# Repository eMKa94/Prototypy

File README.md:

# Prototypy

This repository contains projects modules ( schematics with PCB's layouts ).
The idea is to simply use this schematics as a hierarchical schematics in kicad projects and PCB layouts as reference.

example:

"3V_4I_ac_afe" consist of submodules "ac_i_afe" & "ac_v_afe" ( schematics ). PCB design in kicad cannot be modular so the PCB have to be designed individualy for each design.

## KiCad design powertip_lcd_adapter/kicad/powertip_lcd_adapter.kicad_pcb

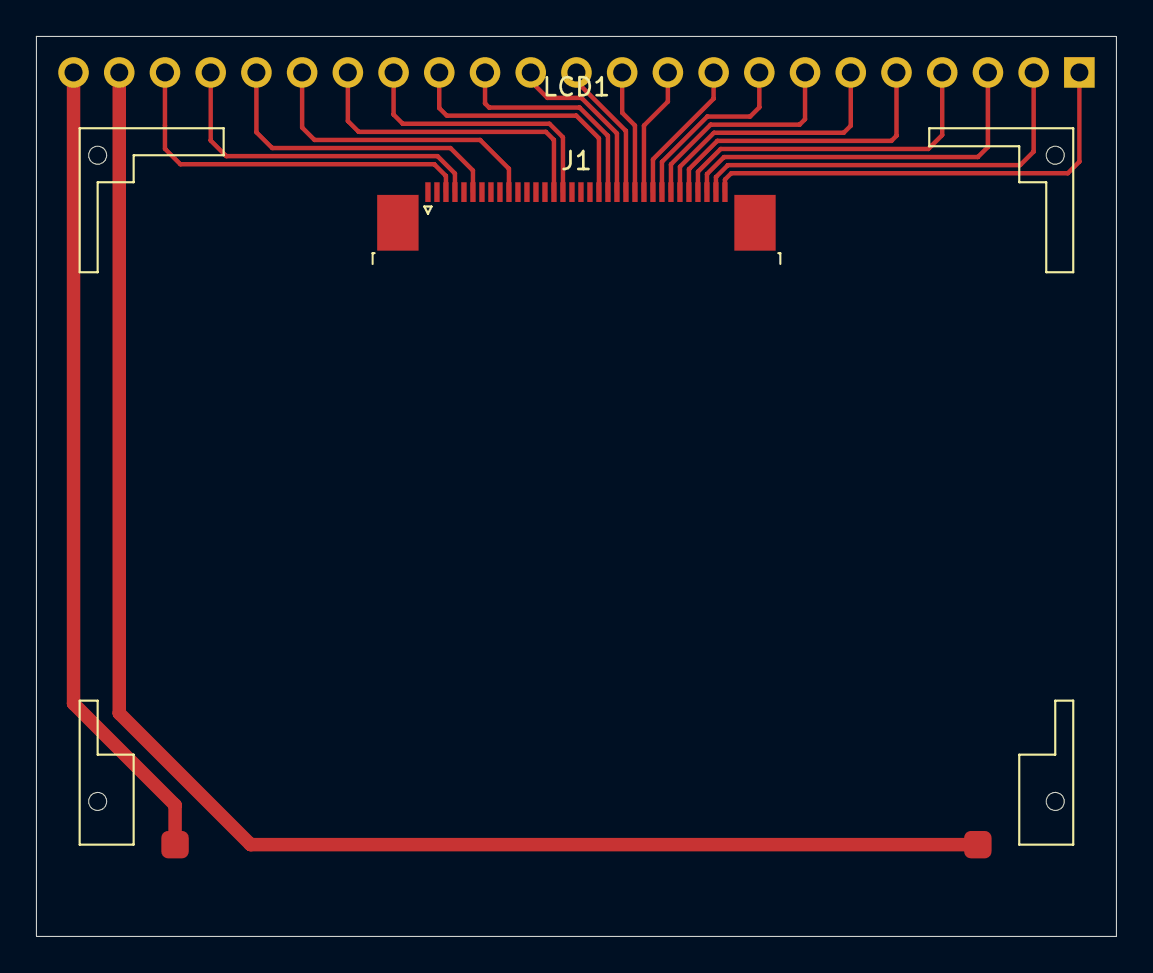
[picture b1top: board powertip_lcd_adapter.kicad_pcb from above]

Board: 2 copper layers, 60.0 x 50.0 mm, 3 parts (1 on the bottom side), 23 nets.

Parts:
J1: Conn_01x34; TE_3-1734839-4_1x34-1MP_P0.5mm_Horizontal
J2: Conn_01x23; PinHeader_1x23_P2.54mm_Vertical
LCD1: lcd_module; LCD_PE12864WRF-055-H-Q

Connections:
/A: J2.22, LCD1.2
/A_0: J1.32, J2.3
/C86: J1.4, J2.20
/CS_1: J1.34, J2.1
/D_0: J1.29, J2.6
/D_1: J1.28, J2.7
/D_2: J1.27, J2.8
/D_3: J1.26, J2.9
/D_4: J1.25, J2.10
/D_5: J1.24, J2.11
/D_6: J1.23, J2.12
/D_7: J1.22, J2.13
/K: J2.23, LCD1.1
/P_S: J1.3, J2.21
/RD: J1.30, J2.5
/RST: J1.33, J2.2
/VDD: J1.21, J2.14
/VG: J1.6, J2.19
/VM: J1.10, J2.18
/VSS: J1.20, J2.15
/V_0: J1.16, J2.16
/WR: J1.31, J2.4
/XV_0: J1.15, J2.17

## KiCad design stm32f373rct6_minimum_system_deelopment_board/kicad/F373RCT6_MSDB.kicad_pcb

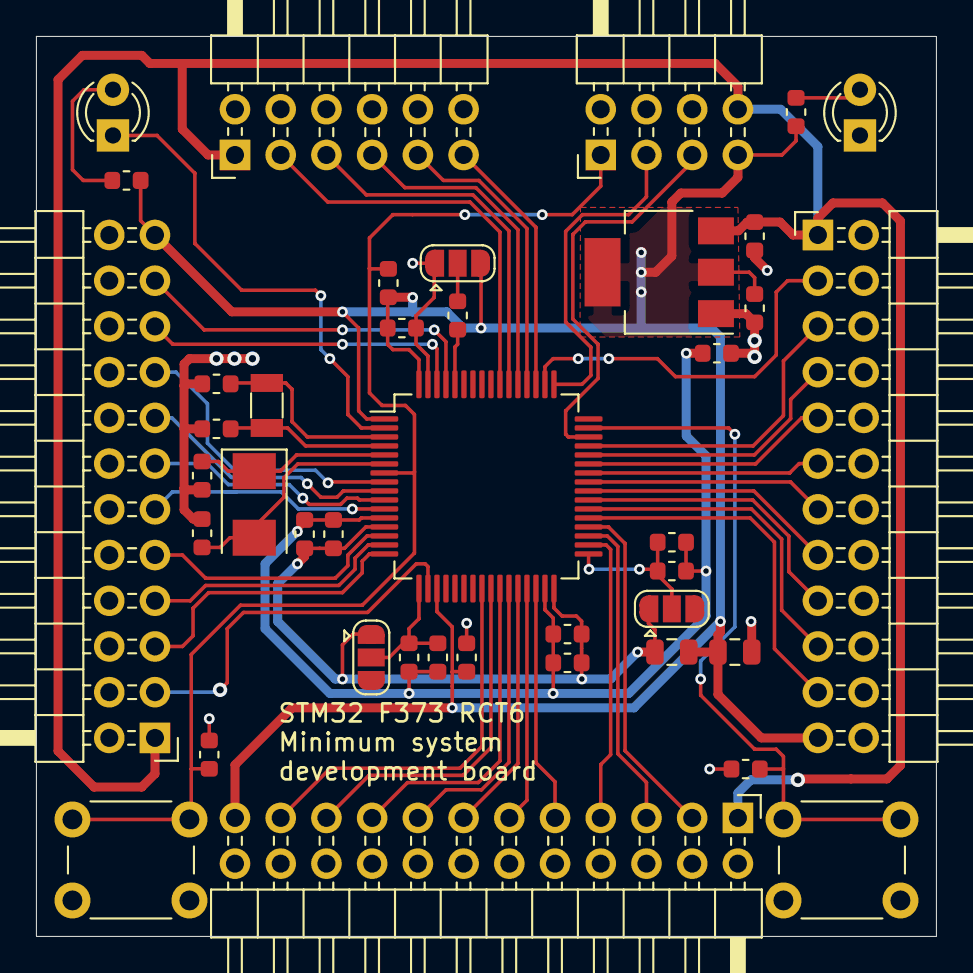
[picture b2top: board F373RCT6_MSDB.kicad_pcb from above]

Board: 2 copper layers, 50.0 x 50.0 mm, 41 parts (0 on the bottom side), 55 nets.

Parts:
C1, C8, C10, C12, C17: 10n; C_0603_1608Metric
C2, C3: 22p; C_0603_1608Metric
C4, C5: 12p; C_0603_1608Metric
C6, C9, C11, C13, C18: 1u; C_0603_1608Metric
C7, C14, C15, C19: 100n; C_0603_1608Metric
C16: 4,7u; C_0805_2012Metric
D1, D2: LED; LED_D3.0mm
J1: Conn_02x04_Odd_Even; PinHeader_2x04_P2.54mm_Horizontal
J2: Conn_02x06_Odd_Even; PinHeader_2x06_P2.54mm_Horizontal
J3, J4, J5: Conn_02x12_Odd_Even; PinHeader_2x12_P2.54mm_Horizontal
JP1: Jumper_VREFSD; SolderJumper-3_P1.3mm_Open_RoundedPad1.0x1.5mm
JP2: Jumper_VREF; SolderJumper-3_P1.3mm_Open_RoundedPad1.0x1.5mm
JP3: Jumper_BOOT0; SolderJumper-3_P1.3mm_Open_RoundedPad1.0x1.5mm
L1: 10u; L_0805_2012Metric
R1, R2: 10K; R_0603_1608Metric
R3: 0; R_0603_1608Metric
R4, R5: 510; R_0603_1608Metric
SW1: SW_RESET; SW_PUSH_6mm_H7.3mm
SW2: SW_F6; SW_PUSH_6mm_H7.3mm
U1: STM32F373RCTx; LQFP-64_10x10mm_P0.5mm
U2: LM1117-3.3; SOT-223-3_TabPin2
Y1: 8M; Crystal_SMD_5032-2Pin_5.0x3.2mm
Y2: 32768; Crystal_SMD_3215-2Pin_3.2x1.5mm

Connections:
+5V: C17.1, J1.8, J2.1, J3.1, J4.1, J5.1, U2.3
/A_0: J3.9, U1.14
/A_1: J3.7, U1.15
/A_2: J3.5, U1.16
/A_3: J3.3, U1.18
/A_8: J5.13, U1.41
/A_9: J5.11, U1.42
/A_10: J5.9, U1.43
/A_11: J5.7, U1.44
/A_12: J5.5, U1.45
/A_15: J5.3, U1.50
/B_0: J4.17, U1.26
/B_1: J4.15, U1.27
/B_2: J4.13, U1.28
/B_3: J2.3, U1.55
/B_8: J3.21, U1.61
/B_9: J3.19, U1.62
/B_14: J4.7, U1.34
/B_15: J4.5, U1.35
/C_0: J3.17, U1.8
/C_1: J3.15, U1.9
/C_2: J3.13, U1.10
/C_3: J3.11, U1.11
/C_4: J4.21, U1.24
/C_5: J4.19, U1.25
/C_6: J5.21, U1.37
/C_7: J5.19, U1.38
/C_8: J5.17, U1.39
/C_9: J5.15, U1.40
/C_10: J2.11, U1.51
/C_11: J2.9, U1.52
/C_12: J2.7, U1.53
/C_13: D1.1, U1.2
/D_2: J2.5, U1.54
/D_8: J4.3, U1.36
/E_8: J4.11, U1.29
/E_9: J4.9, U1.30
/F_6: C19.2, SW2.1, U1.47
/STM32F373RCT6/BOOT0: JP3.2, R1.1
/STM32F373RCT6/GNDA: C1.2, C6.2, C8.2, C9.2, C10.2, C11.2, C12.2, C13.2, R3.2, U1.12, U1.31
/STM32F373RCT6/VDDA: C1.1, C6.1, C8.1, C9.1, JP1.1, JP2.1, L1.1, U1.13, U1.32
/STM32F373RCT6/VREF+: C12.1, C13.1, JP2.2, U1.17
/STM32F373RCT6/VREFSD+: C10.1, C11.1, JP1.2, U1.33
/SWD_CLK: J1.3, U1.49
/SWD_DIO: J1.5, U1.46
/~uC_RESET: C7.2, J1.1, R2.1, SW1.1, U1.7
GND: C2.2, C3.2, C4.2, C5.2, C7.1, C14.2, C15.2, C16.2, C17.2, C18.2, C19.1, D2.1, J1.2, J1.4, J1.6, J2.2, J2.4, J2.6, J2.8, J2.10, J2.12, J3.2, J3.4, J3.6, J3.8, J3.10, J3.12, J3.14, J3.16, J3.18, J3.20, J3.22, J3.24, J4.2, J4.4, J4.6, J4.8, J4.10, J4.12, J4.14, J4.16, J4.18, J4.20, J4.22, J4.24, J5.2, J5.4, J5.6, J5.8, J5.10, J5.12, J5.14, J5.16, J5.18, J5.20, J5.22, J5.24, JP3.1, R3.1, SW1.2, SW2.2, U1.63, U2.1
unnamed: C2.1, U1.5, Y1.1
unnamed: C3.1, U1.6, Y1.2
unnamed: C4.1, U1.3, Y2.1
unnamed: C5.1, U1.4, Y2.2
unnamed: D1.2, R4.2
unnamed: D2.2, R5.2
unnamed: R1.2, U1.60
VDD: C14.1, C15.1, C16.1, C18.1, J1.7, J3.23, J4.23, J5.23, JP3.3, L1.2, R2.2, R4.1, R5.1, U1.1, U1.19, U1.64, U2.2

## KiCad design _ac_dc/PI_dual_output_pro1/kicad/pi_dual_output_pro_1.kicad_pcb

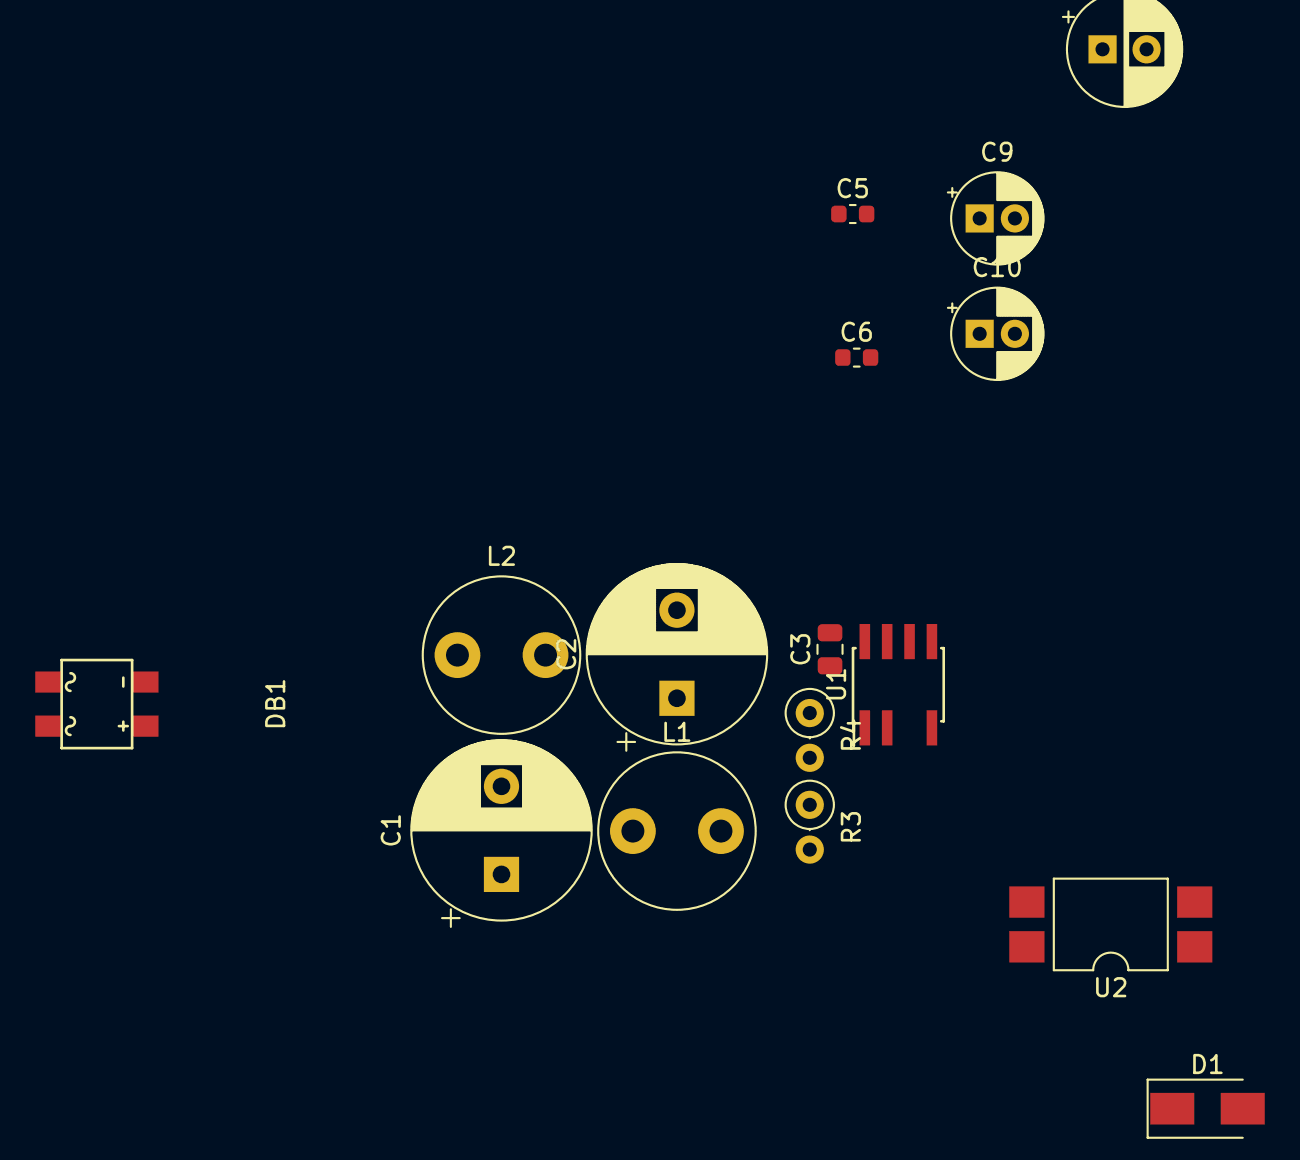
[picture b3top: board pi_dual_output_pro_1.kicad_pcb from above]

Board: 2 copper layers, 16 parts (0 on the bottom side), 9 nets, no tracks yet.

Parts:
C1, C2: 6,8u; CP_Radial_D10.0mm_P5.00mm
C3: 10u; C_0805_2012Metric
C5, C6: 560p; C_0603_1608Metric
C7: 220u; CP_Radial_D6.3mm_P2.50mm
C9, C10: 100u; CP_Radial_D5.0mm_P2.00mm
D1: SMB6F100AY; D_SMA
DB1: D_Bridge_AA+-; MiniDIP
L1, L2: 1m; L_Radial_D8.7mm_P5.00mm_Fastron_07HCP
R3, R4: 2M; R_Axial_DIN0207_L6.3mm_D2.5mm_P2.54mm_Vertical
U1: TNY285D; PowerIntegrations_SO-8C
U2: LTV-817S; SMDIP-4_W9.53mm

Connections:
/hv_dc_+: C1.1, DB1.3, L1.1
/hv_dc_-: C1.2, DB1.4, L2.1
unnamed: C2.1, D1.1, L1.2, R3.2
unnamed: C2.2, C3.2, L2.2, U1.5, U1.6, U1.7, U1.8, U2.3
unnamed: C3.1, U1.2
unnamed: C5.1, C7.1
unnamed: C7.2, C9.2
unnamed: R3.1, R4.2
unnamed: R4.1, U1.1, U2.4

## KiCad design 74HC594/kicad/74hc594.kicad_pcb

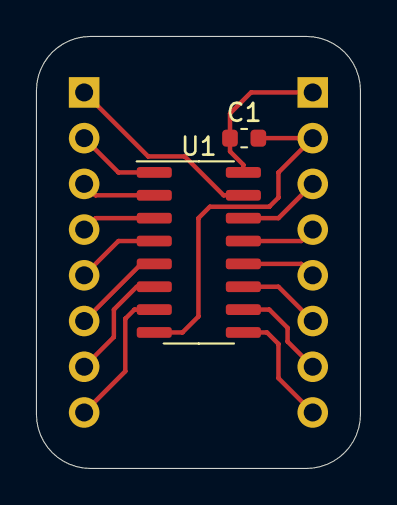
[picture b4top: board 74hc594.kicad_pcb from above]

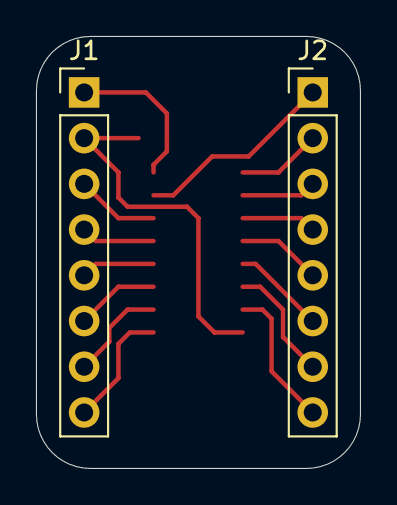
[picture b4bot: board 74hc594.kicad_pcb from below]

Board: 2 copper layers, 18.0 x 24.0 mm, 4 parts (2 on the bottom side), 16 nets.

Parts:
C1: C; C_0603_1608Metric
J1, J2: Conn_01x08; PinHeader_1x08_P2.54mm_Vertical
U1: 74HC595; SOIC-16_3.9x9.9mm_P1.27mm

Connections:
/GND: C1.2, J1.2, U1.8
/Q_A: J2.1, U1.15
/Q_B: J2.2, U1.1
/Q_C: J2.3, U1.2
/Q_D: J2.4, U1.3
/Q_E: J2.5, U1.4
/Q_F: J2.6, U1.5
/Q_G: J2.7, U1.6
/Q_H: J2.8, U1.7
/Q_H': J1.8, U1.9
/RCLK: J1.5, U1.12
/SER: J1.3, U1.14
/SRCLK: J1.6, U1.11
/VCC: C1.1, J1.1, U1.16
/~OE: J1.4, U1.13
/~SRCLR: J1.7, U1.10

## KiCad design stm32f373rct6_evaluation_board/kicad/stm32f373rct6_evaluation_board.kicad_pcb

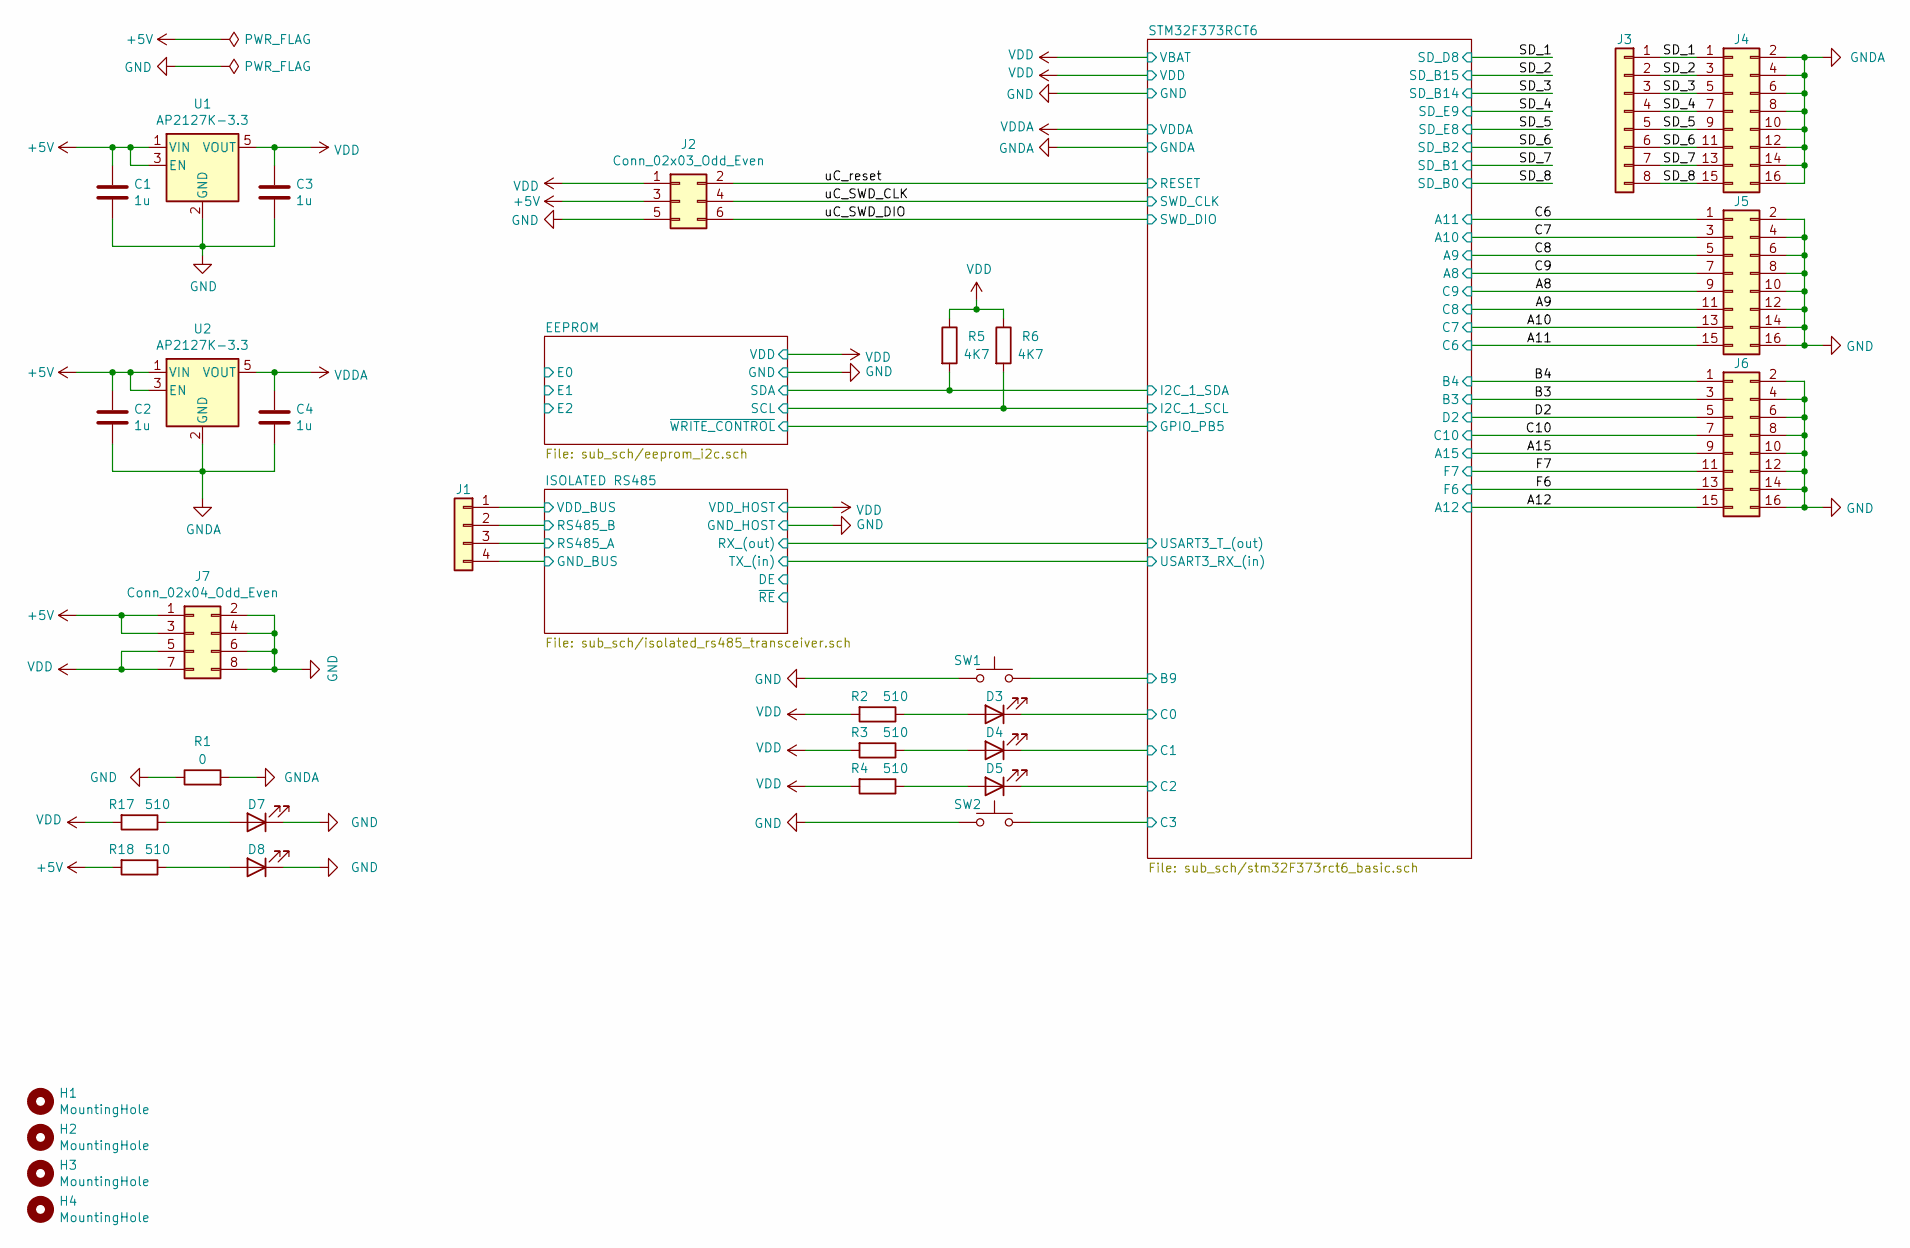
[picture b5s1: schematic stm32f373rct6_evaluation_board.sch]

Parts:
C1, C2, C3, C4: 1u; C_0603_1608Metric
D3, D4, D5, D7, D8: LED; LED_0805_2012Metric
H1, H2, H3, H4: MountingHole; MountingHole_3.2mm_M3
J1: RS485_connector; PinHeader_1x04_P2.54mm_Horizontal
J2: Conn_02x03_Odd_Even; PinHeader_2x03_P2.54mm_Horizontal
J3: Conn_01x08; PinHeader_1x08_P2.54mm_Vertical
J4: Conn_02x08_Odd_Even; PinHeader_2x08_P2.54mm_Horizontal
J5, J6: Conn_02x08_Odd_Even; PinHeader_2x08_P2.54mm_Vertical
J7: Conn_02x04_Odd_Even; PinHeader_2x04_P2.54mm_Vertical
R1: 0; R_0603_1608Metric
R2, R3, R4, R17, R18: 510; R_0402_1005Metric
R5, R6: 4K7; R_0402_1005Metric
SW1, SW2: SW; SW_SPST_B3U-1000P
U1, U2: AP2127K-3.3; SOT-23-5

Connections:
+5V: C1.1, C2.1, J2.3, J7.1, J7.3, R18.2, U1.1 (VIN), U1.3 (EN), U2.1 (VIN), U2.3 (EN)
/A8: J5.9; also elsewhere on the board
/A9: J5.11; also elsewhere on the board
/A10: J5.13; also elsewhere on the board
/A11: J5.15; also elsewhere on the board
/A15: J6.9; also elsewhere on the board
/B3: J6.3; also elsewhere on the board
/B4: J6.1; also elsewhere on the board
/C6: J5.1; also elsewhere on the board
/C7: J5.3; also elsewhere on the board
/C8: J5.5; also elsewhere on the board
/C9: J5.7; also elsewhere on the board
/C10: J6.7; also elsewhere on the board
/D2: J6.5; also elsewhere on the board
/F6: J6.13; also elsewhere on the board
/F7: J6.11; also elsewhere on the board
/ISOLATED RS485/GND_BUS: J1.4; also elsewhere on the board
/ISOLATED RS485/RS485_A: J1.3; also elsewhere on the board
/ISOLATED RS485/RS485_B: J1.2; also elsewhere on the board
/ISOLATED RS485/VDD_BUS: J1.1; also elsewhere on the board
/SD_1: J3.1, J4.1; also elsewhere on the board
/SD_2: J3.2, J4.3; also elsewhere on the board
/SD_3: J3.3, J4.5; also elsewhere on the board
/SD_4: J3.4, J4.7; also elsewhere on the board
/SD_5: J3.5, J4.9; also elsewhere on the board
/SD_6: J3.6, J4.11; also elsewhere on the board
/SD_7: J3.7, J4.13; also elsewhere on the board
/SD_8: J3.8, J4.15; also elsewhere on the board
/STM32F373RCT6/B9: SW1.2; also elsewhere on the board
/STM32F373RCT6/C0: D3.1 (K); also elsewhere on the board
/STM32F373RCT6/C1: D4.1 (K); also elsewhere on the board
/STM32F373RCT6/C2: D5.1 (K); also elsewhere on the board
/STM32F373RCT6/C3: SW2.2; also elsewhere on the board
/STM32F373RCT6/I2C_1_SCL: R6.2; also elsewhere on the board
/STM32F373RCT6/I2C_1_SDA: R5.2; also elsewhere on the board
/uC_SWD_CLK: J2.4; also elsewhere on the board
/uC_SWD_DIO: J2.6; also elsewhere on the board
/uC_reset: J2.2; also elsewhere on the board
GND: C1.2, C3.2, D7.1 (K), D8.1 (K), J2.5, J5.2, J5.4, J5.6, J5.8, J5.10, J5.12, J5.14, J5.16, J6.2, J6.4, J6.6, J6.8, J6.10, J6.12, J6.14, J6.16, J7.2, J7.4, J7.6, J7.8, R1.1, SW1.1, SW2.1, U1.2 (GND); also elsewhere on the board
GNDA: C2.2, C4.2, J4.2, J4.4, J4.6, J4.8, J4.10, J4.12, J4.14, J4.16, R1.2, U2.2 (GND); also elsewhere on the board
GPIO_A12: J6.15; also elsewhere on the board
unnamed: D3.2 (A), R2.1
unnamed: D4.2 (A), R3.1
unnamed: D5.2 (A), R4.1
unnamed: D7.2 (A), R17.1
unnamed: D8.2 (A), R18.1
VDD: C3.1, J2.1, J7.5, J7.7, R2.2, R3.2, R4.2, R5.1, R6.1, R17.2, U1.5 (VOUT); also elsewhere on the board
VDDA: C4.1, U2.5 (VOUT); also elsewhere on the board

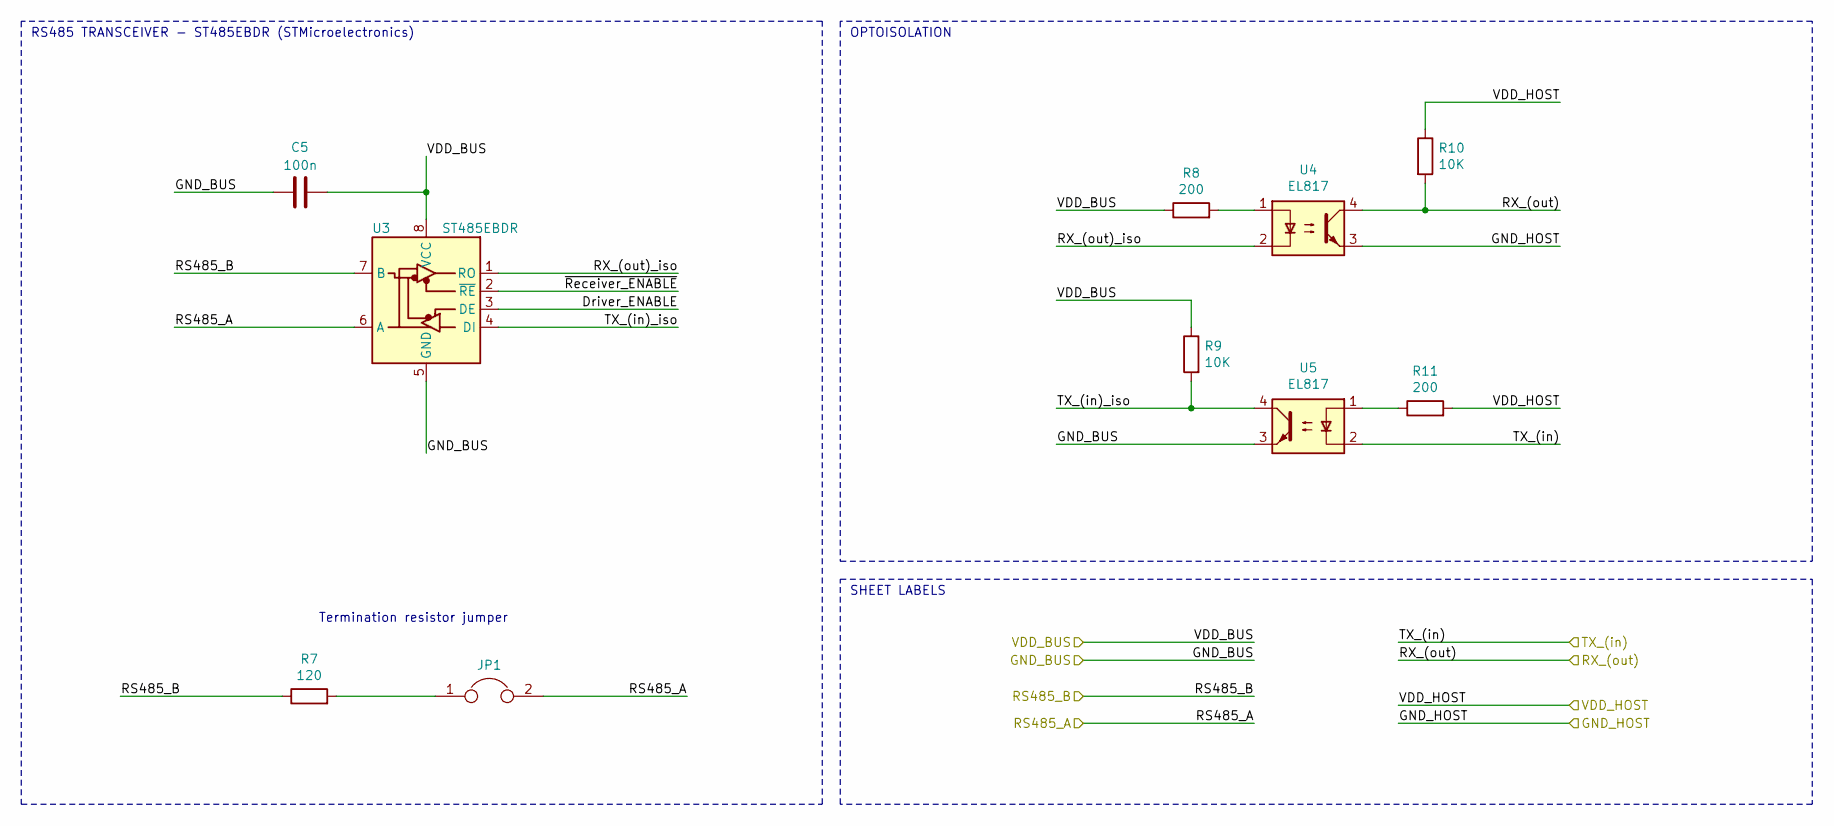
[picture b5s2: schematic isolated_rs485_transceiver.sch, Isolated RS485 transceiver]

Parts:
C5: 100n; C_0603_1608Metric
JP1: Jumper; SolderJumper-2_P1.3mm_Open_RoundedPad1.0x1.5mm
R7: 120; R_0603_1608Metric
R8, R11: 200; R_0603_1608Metric
R9, R10: 10K; R_0603_1608Metric
U3: ST485EBDR; SOIC-8_3.9x4.9mm_P1.27mm
U4, U5: EL817; DIP-4_W7.62mm

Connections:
/ISOLATED RS485/Driver_ENABLE: U3.3 (DE)
/ISOLATED RS485/GND_BUS: C5.1, U3.5 (GND), U5.3; also elsewhere on the board
/ISOLATED RS485/RS485_A: JP1.2, U3.6 (A); also elsewhere on the board
/ISOLATED RS485/RS485_B: R7.1, U3.7 (B); also elsewhere on the board
/ISOLATED RS485/RX_(out): R10.2, U4.4; also elsewhere on the board
/ISOLATED RS485/RX_(out)_iso: U3.1 (RO), U4.2
/ISOLATED RS485/TX_(in): U5.2; also elsewhere on the board
/ISOLATED RS485/TX_(in)_iso: R9.2, U3.4 (DI), U5.4
/ISOLATED RS485/VDD_BUS: C5.2, R8.1, R9.1, U3.8 (VCC); also elsewhere on the board
/ISOLATED RS485/~Receiver_ENABLE: U3.2 (~RE)
GND: U4.3; also elsewhere on the board
unnamed: JP1.1, R7.2
unnamed: R8.2, U4.1
unnamed: R11.1, U5.1
VDD: R10.1, R11.2; also elsewhere on the board

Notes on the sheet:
OPTOISOLATION
RS485 TRANSCEIVER - ST485EBDR (STMicroelectronics)
SHEET LABELS
Termination resistor jumper

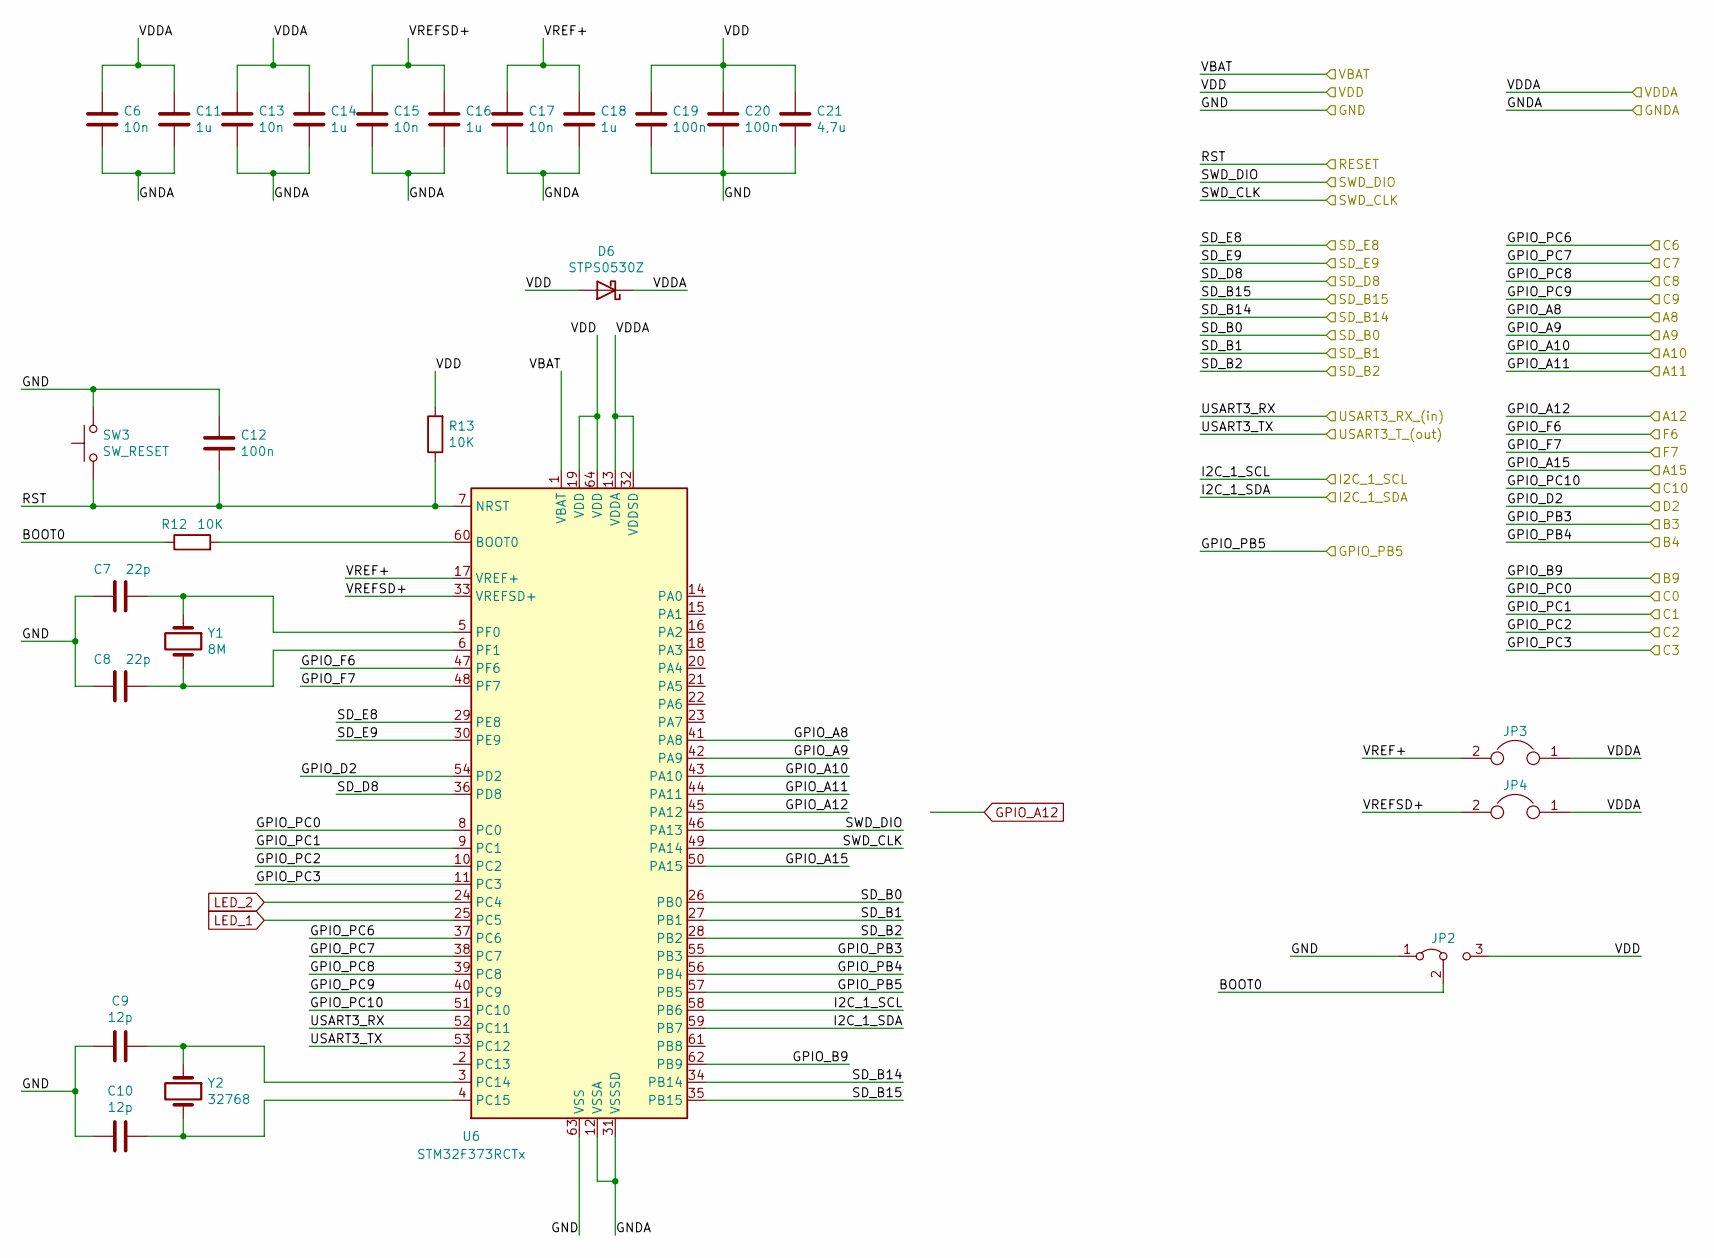
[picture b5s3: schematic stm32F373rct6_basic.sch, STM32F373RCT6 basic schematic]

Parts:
C6, C13, C15, C17: 10n; C_0402_1005Metric
C7, C8: 22p; C_0603_1608Metric
C9, C10: 12p; C_0603_1608Metric
C11, C14, C16, C18: 1u; C_0603_1608Metric
C12: 100n; C_0603_1608Metric
C19, C20: 100n; C_0402_1005Metric
C21: 4,7u; C_0805_2012Metric
D6: STPS0530Z; D_SOD-323
JP2: Jumper_BOOT0; SolderJumper-3_P1.3mm_Open_RoundedPad1.0x1.5mm
JP3, JP4: Jumper; SolderJumper-2_P1.3mm_Open_RoundedPad1.0x1.5mm
R12, R13: 10K; R_0402_1005Metric
SW3: SW_RESET; SW_SPST_B3U-1000P
U6: STM32F373RCTx; LQFP-64_10x10mm_P0.5mm
Y1: 8M; Crystal_SMD_5032-2Pin_5.0x3.2mm; PART_NUMBER LF XTAL003151
Y2: 32768; Crystal_SMD_3215-2Pin_3.2x1.5mm

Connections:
/A8: U6.40 (PC9); also elsewhere on the board
/A9: U6.39 (PC8); also elsewhere on the board
/A10: U6.38 (PC7); also elsewhere on the board
/A11: U6.37 (PC6); also elsewhere on the board
/A15: U6.50 (PA15); also elsewhere on the board
/B3: U6.55 (PB3); also elsewhere on the board
/B4: U6.56 (PB4); also elsewhere on the board
/C6: U6.44 (PA11); also elsewhere on the board
/C7: U6.43 (PA10); also elsewhere on the board
/C8: U6.42 (PA9); also elsewhere on the board
/C9: U6.41 (PA8); also elsewhere on the board
/C10: U6.51 (PC10); also elsewhere on the board
/D2: U6.54 (PD2); also elsewhere on the board
/F6: U6.47 (PF6); also elsewhere on the board
/F7: U6.48 (PF7); also elsewhere on the board
/ISOLATED RS485/RX_(out): U6.52 (PC11); also elsewhere on the board
/ISOLATED RS485/TX_(in): U6.53 (PC12); also elsewhere on the board
/SD_1: U6.36 (PD8); also elsewhere on the board
/SD_2: U6.35 (PB15); also elsewhere on the board
/SD_3: U6.34 (PB14); also elsewhere on the board
/SD_4: U6.30 (PE9); also elsewhere on the board
/SD_5: U6.29 (PE8); also elsewhere on the board
/SD_6: U6.28 (PB2); also elsewhere on the board
/SD_7: U6.27 (PB1); also elsewhere on the board
/SD_8: U6.26 (PB0); also elsewhere on the board
/STM32F373RCT6/B9: U6.62 (PB9); also elsewhere on the board
/STM32F373RCT6/BOOT0: JP2.2 (C), R12.1
/STM32F373RCT6/C0: U6.8 (PC0); also elsewhere on the board
/STM32F373RCT6/C1: U6.9 (PC1); also elsewhere on the board
/STM32F373RCT6/C2: U6.10 (PC2); also elsewhere on the board
/STM32F373RCT6/C3: U6.11 (PC3); also elsewhere on the board
/STM32F373RCT6/GPIO_PB5: U6.57 (PB5); also elsewhere on the board
/STM32F373RCT6/I2C_1_SCL: U6.58 (PB6); also elsewhere on the board
/STM32F373RCT6/I2C_1_SDA: U6.59 (PB7); also elsewhere on the board
/STM32F373RCT6/VREF+: C17.1, C18.1, JP3.2, U6.17 (VREF+)
/STM32F373RCT6/VREFSD+: C15.1, C16.1, JP4.2, U6.33 (VREFSD+)
/uC_SWD_CLK: U6.49 (PA14); also elsewhere on the board
/uC_SWD_DIO: U6.46 (PA13); also elsewhere on the board
/uC_reset: C12.2, R13.1, SW3.1, U6.7 (NRST); also elsewhere on the board
GND: C7.2, C8.2, C9.2, C10.2, C12.1, C19.2, C20.2, C21.2, JP2.1 (A), SW3.2, U6.63 (VSS); also elsewhere on the board
GNDA: C6.2, C11.2, C13.2, C14.2, C15.2, C16.2, C17.2, C18.2, U6.12 (VSSA), U6.31 (VSSSD); also elsewhere on the board
GPIO_A12: U6.45 (PA12); also elsewhere on the board
LED_1: U6.25 (PC5)
LED_2: U6.24 (PC4)
unnamed: C7.1, U6.5 (PF0), Y1.1
unnamed: C8.1, U6.6 (PF1), Y1.2
unnamed: C9.1, U6.3 (PC14), Y2.1
unnamed: C10.1, U6.4 (PC15), Y2.2
unnamed: R12.2, U6.60 (BOOT0)
VDD: C19.1, C20.1, C21.1, D6.2 (A), JP2.3 (B), R13.2, U6.1 (VBAT), U6.19 (VDD), U6.64 (VDD); also elsewhere on the board
VDDA: C6.1, C11.1, C13.1, C14.1, D6.1 (K), JP3.1, JP4.1, U6.13 (VDDA), U6.32 (VDDSD); also elsewhere on the board

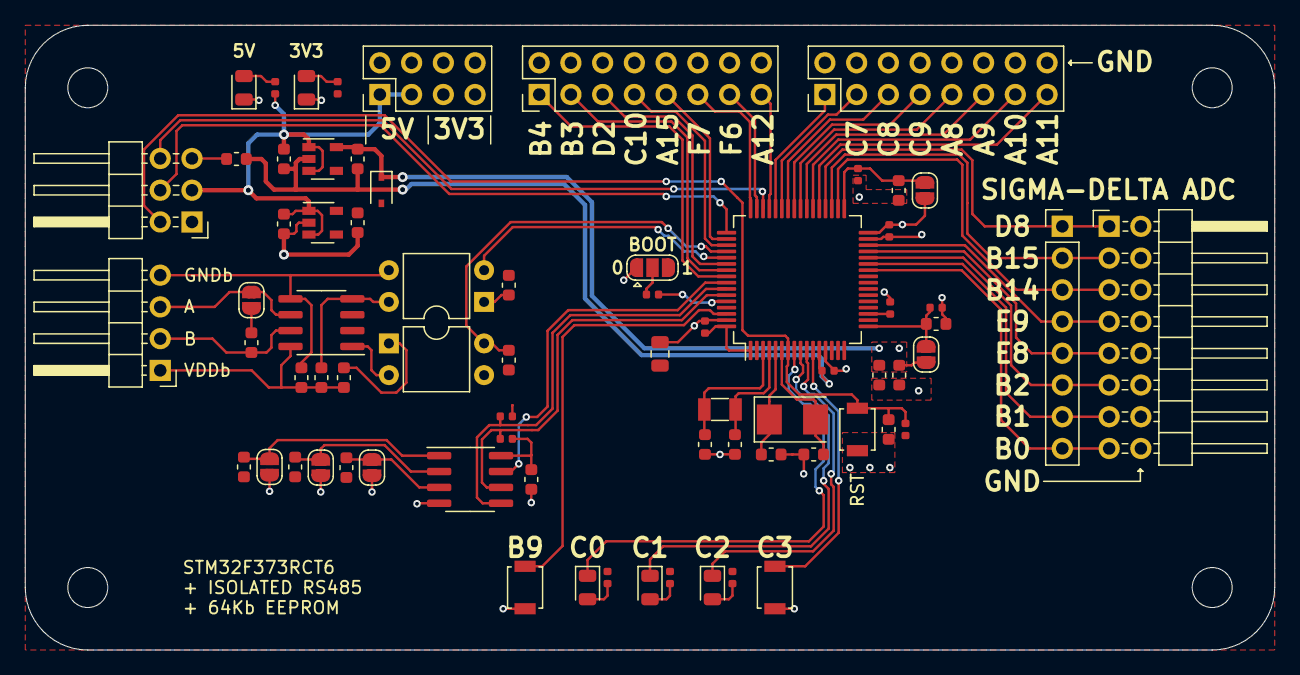
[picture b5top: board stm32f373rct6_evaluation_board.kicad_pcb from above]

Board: 2 copper layers, 100.0 x 50.0 mm, 76 parts (0 on the bottom side), 67 nets.

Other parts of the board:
C22: 100n; C_0603_1608Metric
JP5, JP6, JP7: Jumper; SolderJumper-2_P1.3mm_Open_RoundedPad1.0x1.5mm
R14, R15, R16: 47K; R_0603_1608Metric
U7: M24C64-FDW; SOIC-8_3.9x4.9mm_P1.27mm

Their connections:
/EEPROM/E0: JP7.2, R16.2, U7.1
/EEPROM/E1: JP6.2, R15.2, U7.2
/EEPROM/E2: JP5.2, R14.2, U7.3
/STM32F373RCT6/GPIO_PB5: U7.7; also elsewhere on the board
/STM32F373RCT6/I2C_1_SCL: U7.5; also elsewhere on the board
/STM32F373RCT6/I2C_1_SDA: U7.6; also elsewhere on the board
GND: C22.1, JP5.1, JP6.1, JP7.1, U7.4; also elsewhere on the board
VDD: C22.2, R14.1, R15.1, R16.1, U7.8; also elsewhere on the board

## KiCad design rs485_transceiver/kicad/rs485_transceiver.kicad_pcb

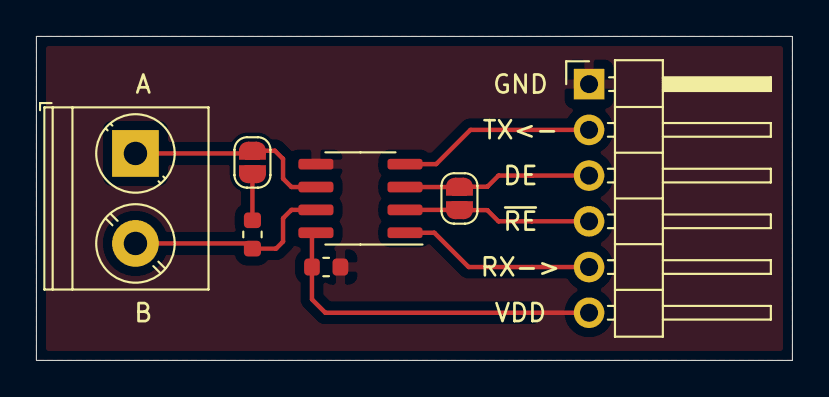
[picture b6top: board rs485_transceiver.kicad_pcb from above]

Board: 2 copper layers, 42.0 x 18.0 mm, 7 parts (0 on the bottom side), 9 nets.

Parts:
C17: 100n; C_0603_1608Metric
J1: Conn_01x02; TerminalBlock_Phoenix_PT-1,5-2-5.0-H_1x02_P5.00mm_Horizontal
J2: Conn_01x06; PinHeader_1x06_P2.54mm_Horizontal
JP8, JP14: Jumper; SolderJumper-2_P1.3mm_Open_RoundedPad1.0x1.5mm
R19: 120; R_0603_1608Metric
U3: ST485EBDR; SOIC-8_3.9x4.9mm_P1.27mm

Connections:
/Driver_ENABLE: J2.3, JP8.2, U3.3
/GND: C17.1, J2.1, U3.5
/RS485_A: J1.1, JP14.2, U3.6
/RS485_B: J1.2, R19.1, U3.7
/RX_(out): J2.5, U3.1
/TX_(in): J2.2, U3.4
/VDD: C17.2, J2.6, U3.8
/~Receiver_ENABLE: J2.4, JP8.1, U3.2
unnamed: JP14.1, R19.2
